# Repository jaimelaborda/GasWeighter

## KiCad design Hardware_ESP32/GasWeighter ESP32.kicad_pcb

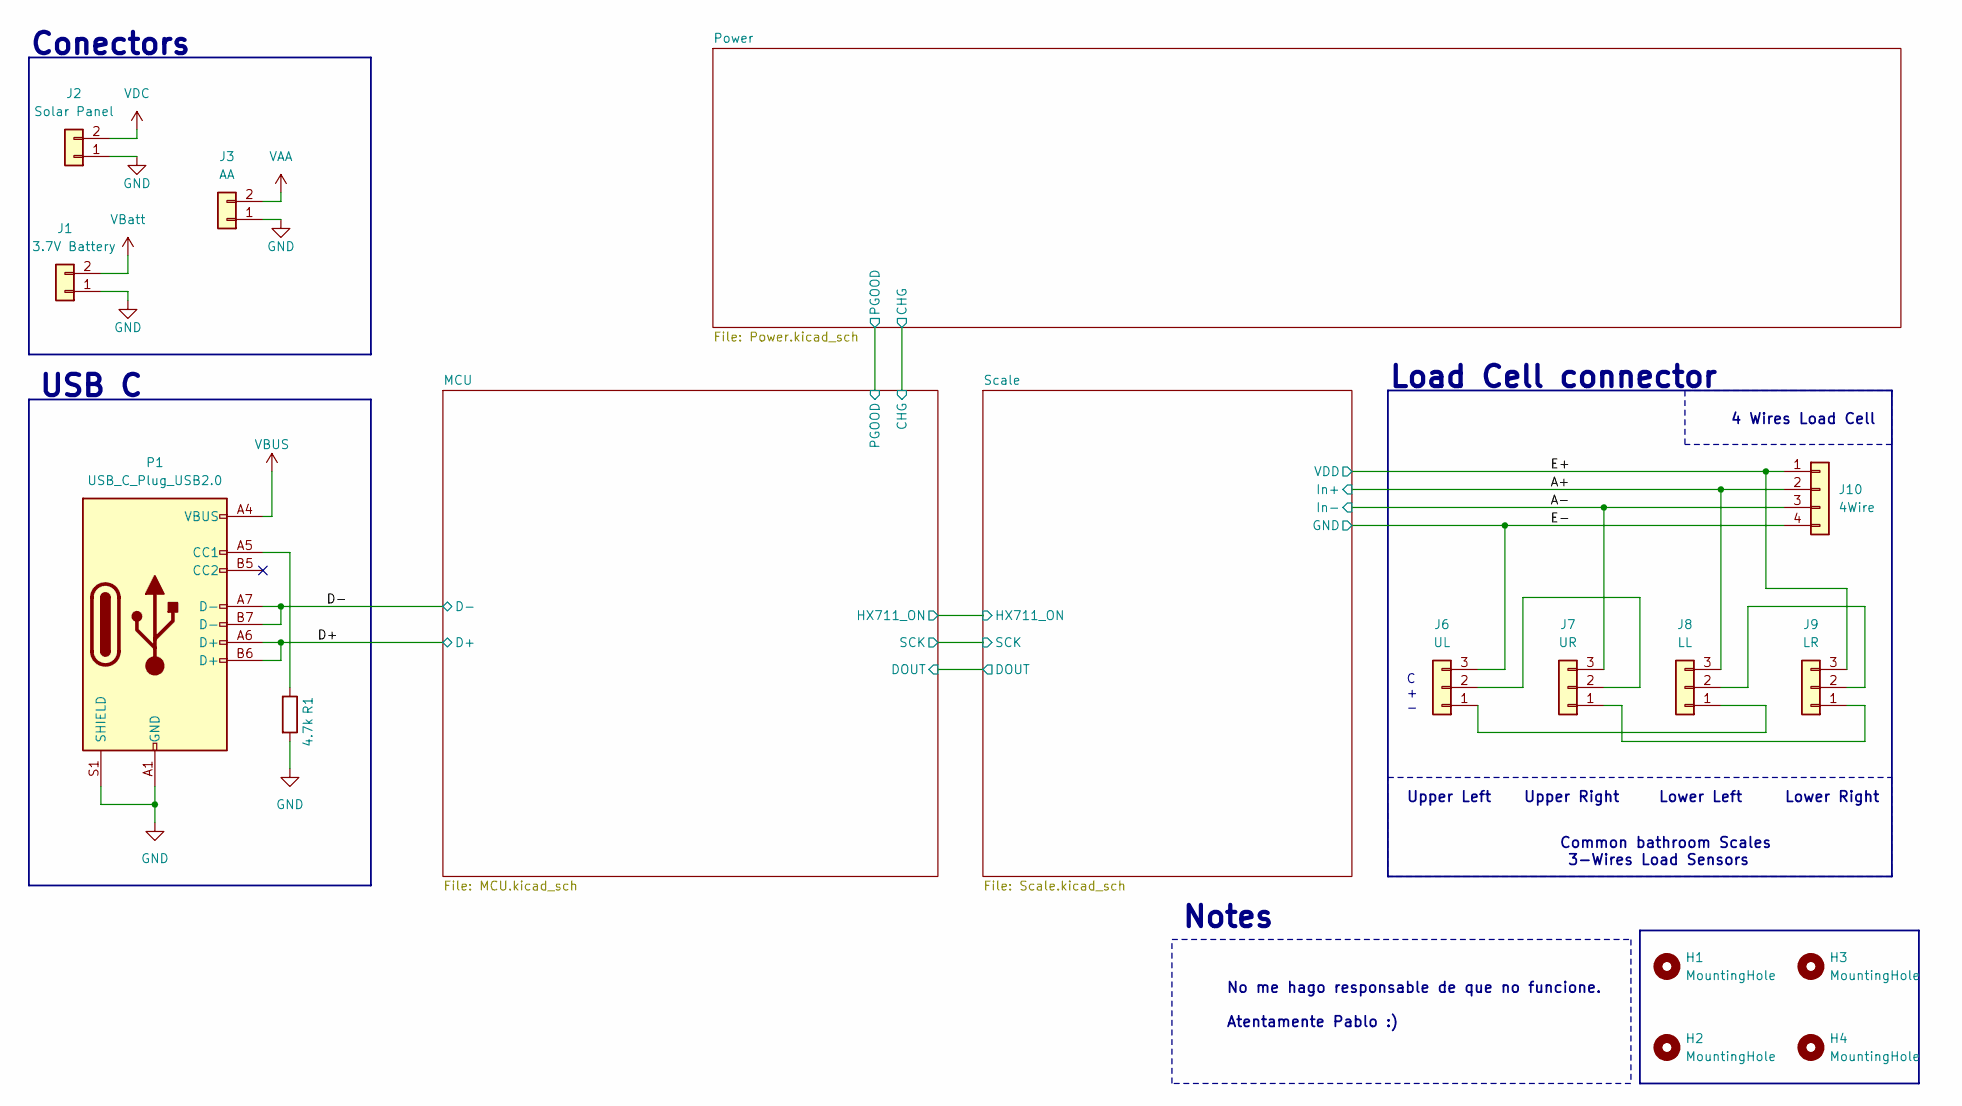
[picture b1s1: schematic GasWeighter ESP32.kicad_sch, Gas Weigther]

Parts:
H1, H2, H3, H4: MountingHole; MountingHole_3.2mm_M3_ISO7380
J1: 3.7V Battery; JST_PH_B2B-PH-K_1x02_P2.00mm_Vertical
J2: Solar Panel; JST_PH_B2B-PH-K_1x02_P2.00mm_Vertical
J3: AA; JST_PH_B2B-PH-K_1x02_P2.00mm_Vertical
J6: UL; JST_PH_B3B-PH-K_1x03_P2.00mm_Vertical
J7: UR; JST_PH_B3B-PH-K_1x03_P2.00mm_Vertical
J8: LL; JST_PH_B3B-PH-K_1x03_P2.00mm_Vertical
J9: LR; JST_PH_B3B-PH-K_1x03_P2.00mm_Vertical
J10: 4Wire; JST_PH_B4B-PH-K_1x04_P2.00mm_Vertical
P1: USB_C_Plug_USB2.0; USB C Molex_1
R1: 4.7k; R_0805_2012Metric_Pad1.20x1.40mm_HandSolder

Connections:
/A+: J8.3, J10.2; also elsewhere on the board
/A-: J7.3, J10.3; also elsewhere on the board
/D+: P1.A6 (D+), P1.B6 (D+); also elsewhere on the board
/D-: P1.A7 (D-), P1.B7 (D-); also elsewhere on the board
/E+: J9.3, J10.1; also elsewhere on the board
unnamed: J6.1, J8.1
unnamed: J6.2, J7.2
unnamed: J7.1, J9.1
unnamed: J8.2, J9.2
unnamed: P1.A5 (CC1), R1.1
VAA: J3.2; also elsewhere on the board
VBUS: P1.A4 (VBUS), P1.A9 (VBUS), P1.B4 (VBUS), P1.B9 (VBUS); also elsewhere on the board
VBatt: J1.2; also elsewhere on the board
VDC: J2.2; also elsewhere on the board

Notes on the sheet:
Common bathroom Scales 3-Wires Load Sensors
Notes
Upper Left
No me hago responsable de que no funcione. Atentamente Pablo :)
C + -
Load Cell connector
Conectors
USB C
Lower Left
Upper Right
4 Wires Load Cell
Lower Right

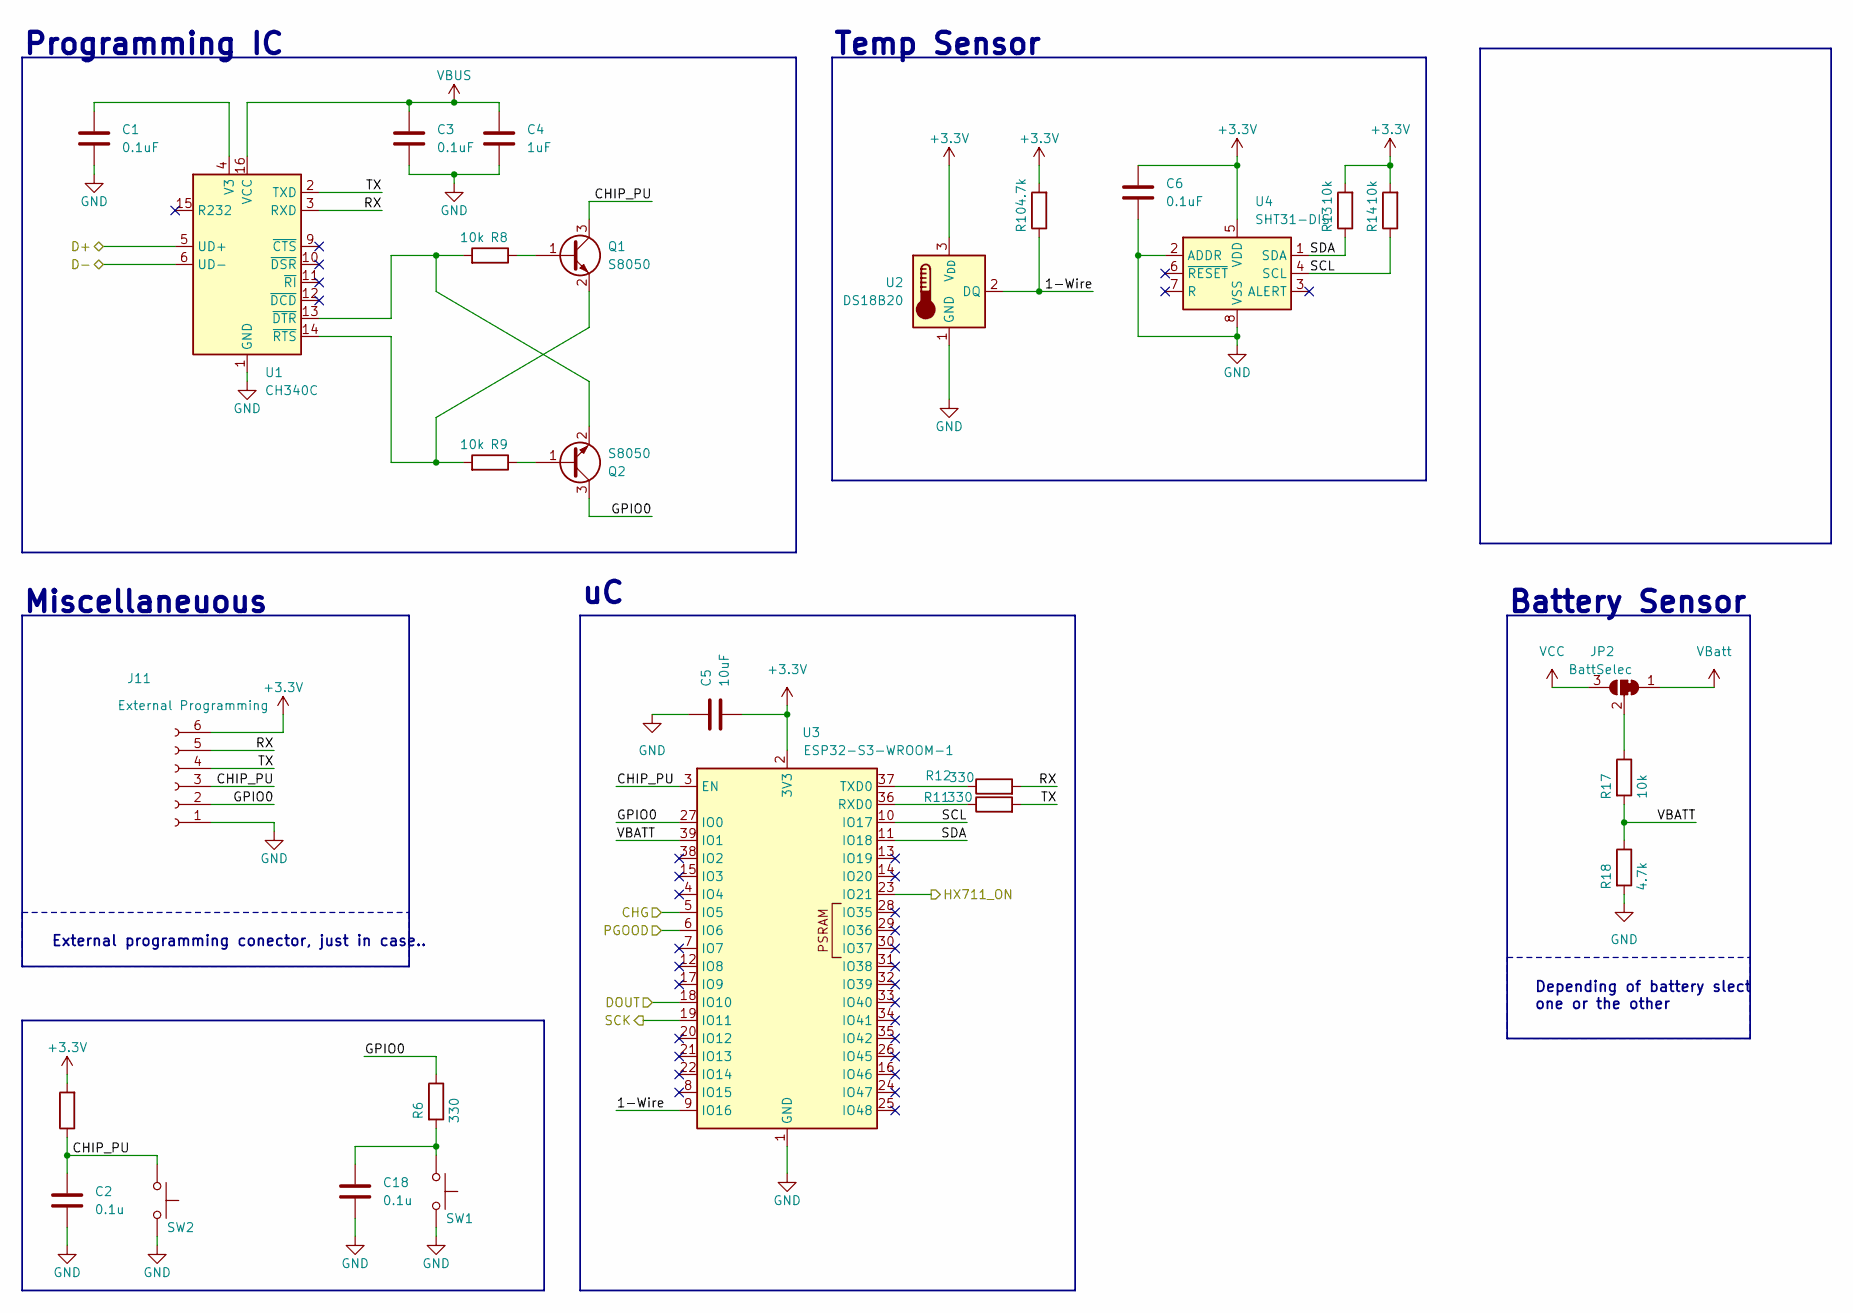
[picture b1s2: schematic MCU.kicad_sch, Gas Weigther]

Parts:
C1, C3, C6: 0.1uF; C_0805_2012Metric
C2, C18: 0.1u; C_0805_2012Metric
C4: 1uF; C_0805_2012Metric
C5: 10uF; C_0805_2012Metric
J11: External Programming; PinHeader_1x06_P2.54mm_Vertical
JP2: BattSelec; SolderJumper-3_P1.3mm_Bridged12_RoundedPad1.0x1.5mm
Q1, Q2: S8050; SOT-23
R5, R8, R9, R13, R14, R17: 10k; R_0805_2012Metric_Pad1.20x1.40mm_HandSolder
R6, R11, R12: 330; R_0805_2012Metric_Pad1.20x1.40mm_HandSolder
R10, R18: 4.7k; R_0805_2012Metric_Pad1.20x1.40mm_HandSolder
SW1, SW2: SW_Push; Button
U1: CH340C; SOIC-16_3.9x9.9mm_P1.27mm
U2: DS18B20; TO-92_Inline
U3: ESP32-S3-WROOM-1
U4: SHT31-DIS; Sensirion_DFN-8-1EP_2.5x2.5mm_P0.5mm_EP1.1x1.7mm

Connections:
/D+: U1.5 (UD+); also elsewhere on the board
/D-: U1.6 (UD-); also elsewhere on the board
/MCU/1-Wire: R10.1, U2.2 (DQ), U3.9 (IO16)
/MCU/CHG: U3.5 (IO5); also elsewhere on the board
/MCU/CHIP_PU: C2.1, J11.3, Q1.3 (C), R5.1, SW2.1, U3.3 (EN)
/MCU/DOUT: U3.18 (IO10); also elsewhere on the board
/MCU/GPIO0: J11.2, Q2.3 (C), R6.1, U3.27 (IO0)
/MCU/HX711_ON: U3.23 (IO21); also elsewhere on the board
/MCU/PGOOD: U3.6 (IO6); also elsewhere on the board
/MCU/RX: J11.5, R12.2, U1.3 (RXD)
/MCU/SCK: U3.19 (IO11); also elsewhere on the board
/MCU/SCL: R14.1, U3.10 (IO17), U4.4 (SCL)
/MCU/SDA: R13.1, U3.11 (IO18), U4.1 (SDA)
/MCU/TX: J11.4, R11.2, U1.2 (TXD)
/MCU/VBATT: R17.2, R18.1, U3.39 (IO1)
unnamed: C18.1, R6.2, SW1.1
unnamed: JP2.2 (C), R17.1
unnamed: Q1.1 (B), R8.1
unnamed: Q1.2 (E), R9.2, U1.14 (~RTS)
unnamed: Q2.1 (B), R9.1
unnamed: Q2.2 (E), R8.2, U1.13 (~DTR)
unnamed: C1.1, U1.4 (V3)
unnamed: R11.1, U3.36 (RXD0)
unnamed: R12.1, U3.37 (TXD0)
VBUS: C3.1, C4.1, U1.16 (VCC); also elsewhere on the board
VBatt: JP2.1 (A); also elsewhere on the board
VCC: JP2.3 (B); also elsewhere on the board

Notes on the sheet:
Programming IC
Temp Sensor
External programming conector, just in case..
Miscellaneuous
Battery Sensor
Depending of battery slect one or the other

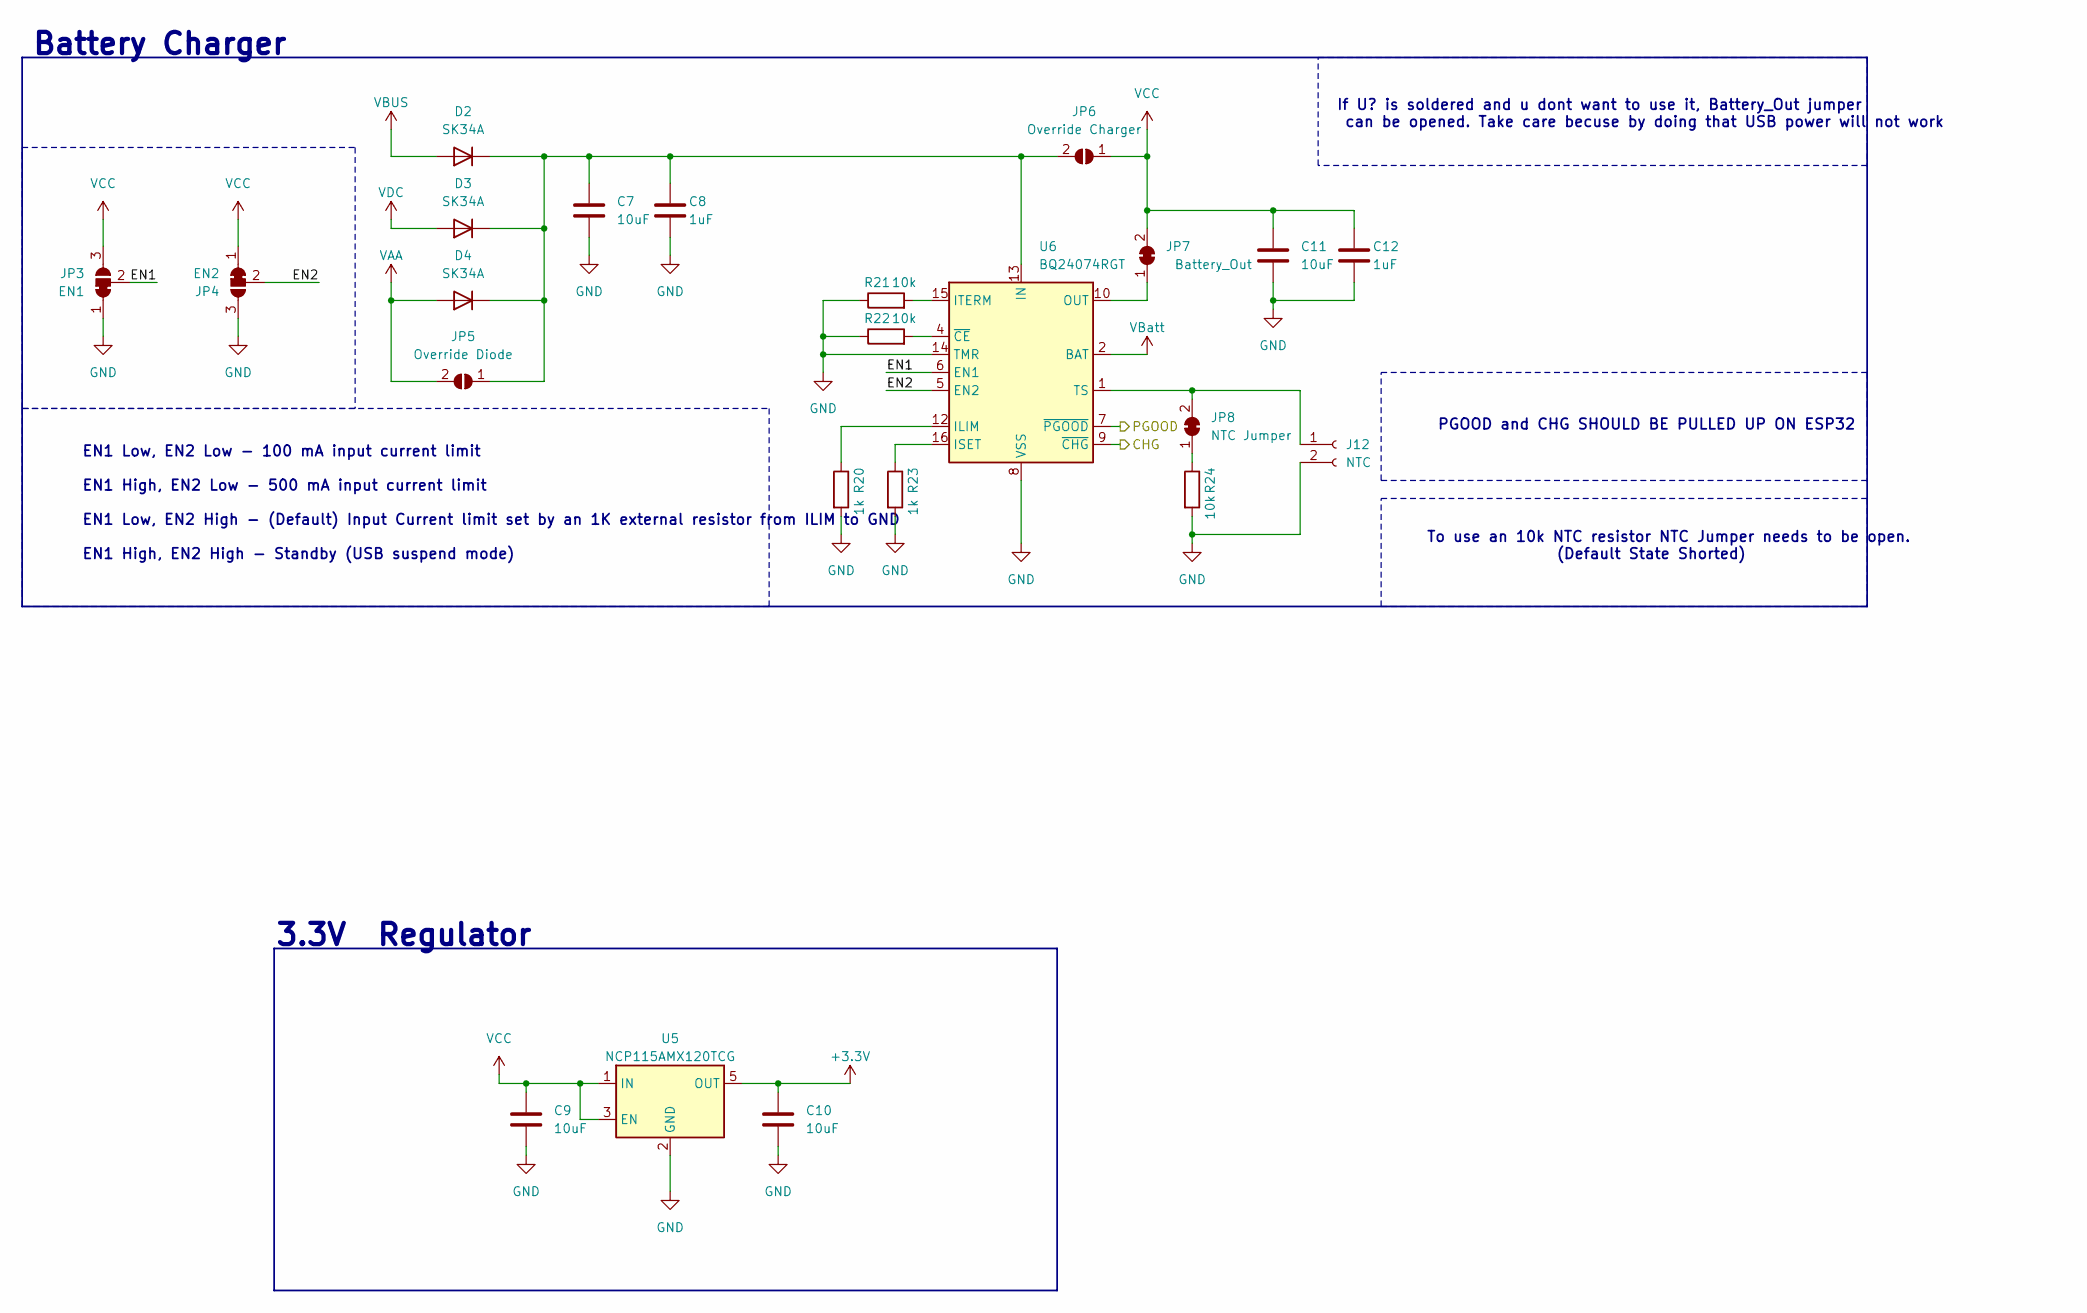
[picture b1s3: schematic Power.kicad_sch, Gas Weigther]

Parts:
C7, C11: 10uF; C_0603_1608Metric_Pad1.08x0.95mm_HandSolder
C8, C12: 1uF; C_0603_1608Metric_Pad1.08x0.95mm_HandSolder
C9, C10: 10uF; C_0805_2012Metric
D2, D3, D4: SK34A; D_0805_2012Metric
J12: NTC; JST_PH_B2B-PH-K_1x02_P2.00mm_Vertical
JP3: EN1; SolderJumper-3_P1.3mm_Bridged12_RoundedPad1.0x1.5mm
JP4: EN2; SolderJumper-3_P1.3mm_Bridged12_RoundedPad1.0x1.5mm
JP5: Override Diode; SolderJumper-2_P1.3mm_Open_RoundedPad1.0x1.5mm
JP6: Override Charger; SolderJumper-2_P1.3mm_Open_RoundedPad1.0x1.5mm
JP7: Battery_Out; SolderJumper-2_P1.3mm_Bridged_RoundedPad1.0x1.5mm
JP8: NTC Jumper; SolderJumper-2_P1.3mm_Bridged_RoundedPad1.0x1.5mm
R20, R23: 1k; R_0805_2012Metric_Pad1.20x1.40mm_HandSolder
R21, R22, R24: 10k; R_0805_2012Metric_Pad1.20x1.40mm_HandSolder
U5: NCP115AMX120TCG; SOT-23-5_HandSoldering
U6: BQ24074RGT; VQFN-16-1EP_3x3mm_P0.5mm_EP1.6x1.6mm

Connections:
/MCU/CHG: U6.9 (~CHG); also elsewhere on the board
/MCU/PGOOD: U6.7 (~PGOOD); also elsewhere on the board
/Power/EN1: JP3.2 (C), U6.6 (EN1)
/Power/EN2: JP4.2 (C), U6.5 (EN2)
unnamed: C7.1, C8.1, D2.1 (K), D3.1 (K), D4.1 (K), JP5.1 (A), JP6.2 (B), U6.13 (IN)
unnamed: J12.1, JP8.2 (B), U6.1 (TS)
unnamed: JP7.1 (A), U6.10 (OUT), U6.11 (OUT)
unnamed: JP8.1 (A), R24.1
unnamed: R20.1, U6.12 (ILIM)
unnamed: R23.1, U6.16 (ISET)
unnamed: R21.2, U6.15 (ITERM)
unnamed: R22.2, U6.4 (~CE)
VAA: D4.2 (A), JP5.2 (B); also elsewhere on the board
VBUS: D2.2 (A); also elsewhere on the board
VBatt: U6.2 (BAT), U6.3 (BAT); also elsewhere on the board
VCC: C9.1, C11.1, C12.1, JP3.3 (B), JP4.1 (A), JP6.1 (A), JP7.2 (B), U5.1 (IN), U5.3 (EN); also elsewhere on the board
VDC: D3.2 (A); also elsewhere on the board

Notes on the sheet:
Battery Charger
EN1 Low, EN2 Low - 100 mA input current limit EN1 High, EN2 Low - 500 mA input current limit EN1 Low, EN2 High - (Default) Input Current limit set by an 1K external resistor from ILIM to GND EN1 High, EN2 High - Standby (USB suspend mode)
3.3V Regulator
If U? is soldered and u dont want to use it, Battery_Out jumper can be opened. Take care becuse by doing that USB power will not work
PGOOD and CHG SHOULD BE PULLED UP ON ESP32
To use an 10k NTC resistor NTC Jumper needs to be open. (Default State Shorted)

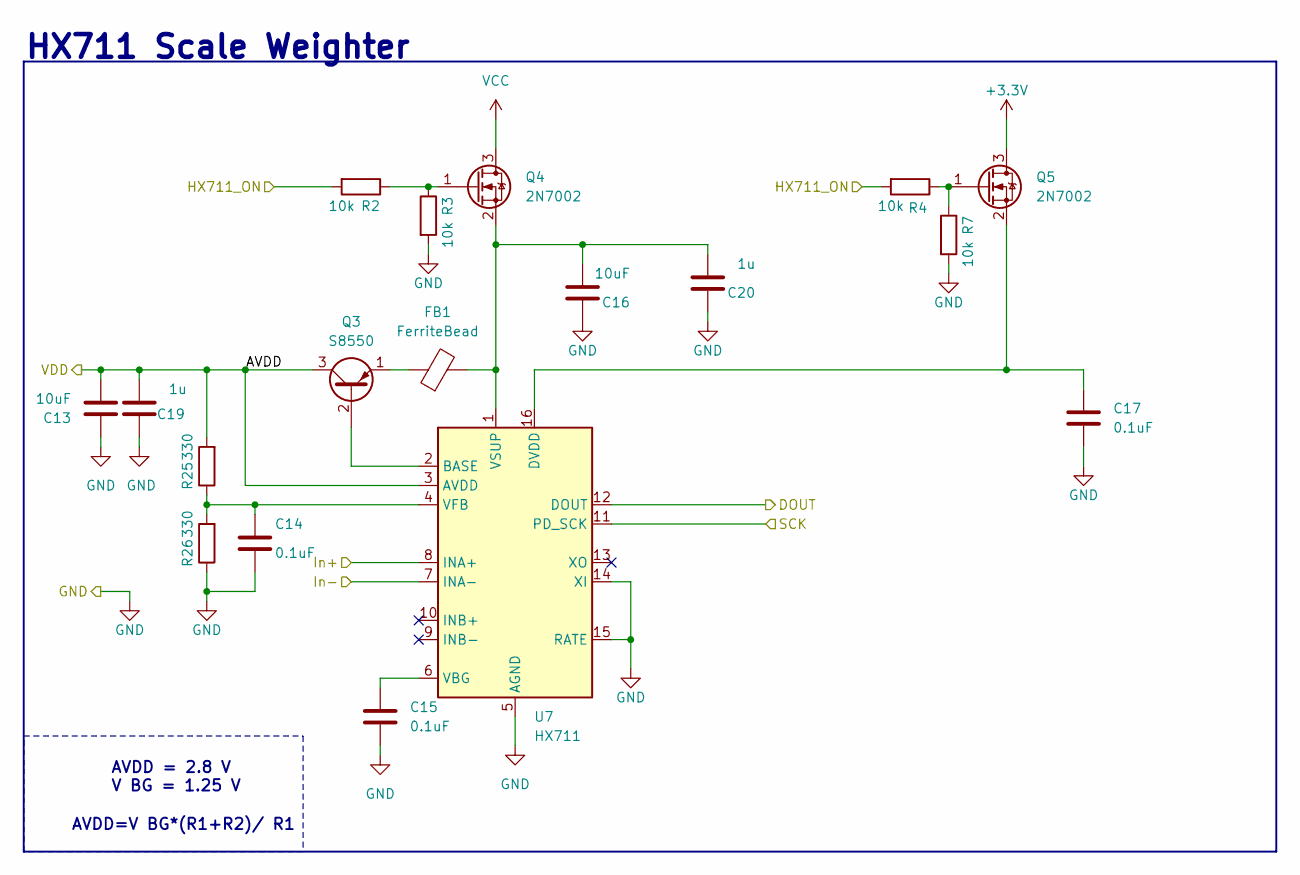
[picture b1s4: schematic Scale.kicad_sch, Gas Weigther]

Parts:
C13, C16: 10uF; C_0805_2012Metric
C14, C15, C17: 0.1uF; C_0805_2012Metric
C19, C20: 1u; C_0805_2012Metric
FB1: FerriteBead; L_0805_2012Metric
Q3: S8550; SOT-23
Q4, Q5: 2N7002; SOT-23
R2, R3, R4, R7: 10k; R_0805_2012Metric_Pad1.20x1.40mm_HandSolder
R25, R26: 330; R_0805_2012Metric_Pad1.20x1.40mm_HandSolder
U7: HX711; SOP-16_3.9x9.9mm_P1.27mm

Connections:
/A+: U7.8 (INA+); also elsewhere on the board
/A-: U7.7 (INA-); also elsewhere on the board
/E+: C13.2, C19.2, Q3.3 (C), R25.2, U7.3 (AVDD); also elsewhere on the board
/MCU/DOUT: U7.12 (DOUT); also elsewhere on the board
/MCU/HX711_ON: R2.2, R4.2; also elsewhere on the board
/MCU/SCK: U7.11 (PD_SCK); also elsewhere on the board
unnamed: Q3.2 (B), U7.2 (BASE)
unnamed: FB1.1, Q3.1 (E)
unnamed: Q4.1 (G), R2.1, R3.1
unnamed: C16.2, C20.2, FB1.2, Q4.2 (S), U7.1 (VSUP)
unnamed: Q5.1 (G), R4.1, R7.1
unnamed: C17.1, Q5.2 (S), U7.16 (DVDD)
unnamed: C15.1, U7.6 (VBG)
unnamed: C14.1, R25.1, R26.2, U7.4 (VFB)
VCC: Q4.3 (D); also elsewhere on the board

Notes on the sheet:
AVDD=V BG*(R1+R2)/ R1
HX711 Scale Weighter
AVDD = 2.8 V V BG = 1.25 V

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
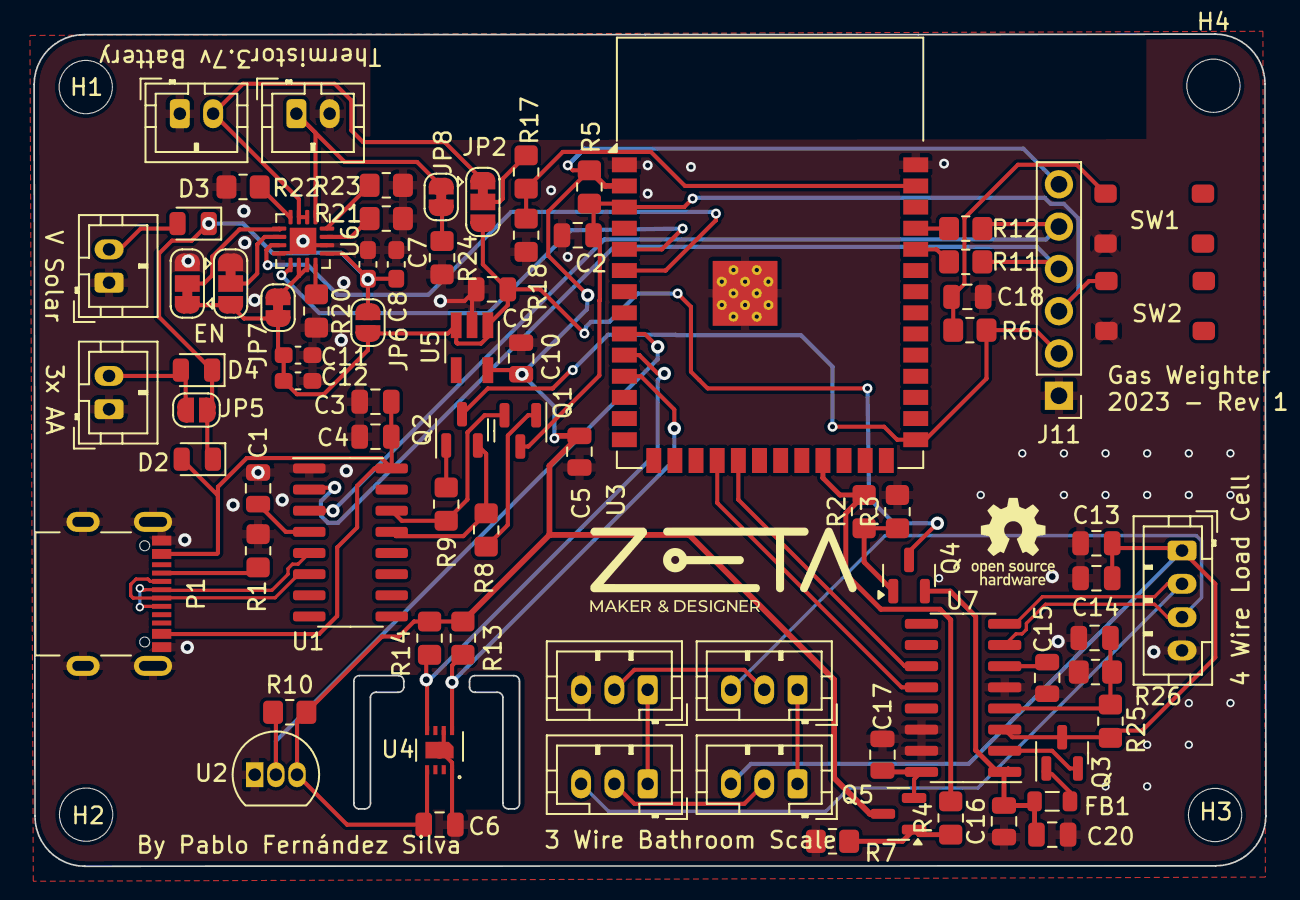
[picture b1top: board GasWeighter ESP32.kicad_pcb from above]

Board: 2 copper layers, 74.0 x 50.0 mm, 83 parts (0 on the bottom side), 57 nets.

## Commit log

2023-11-11 Organized
2023-11-12 3Cents USB
2023-11-12 Gerbers
2024-08-29 ESP32 HW added
    Added a hardware version with ESP32-S3 microcontroller
2024-09-15 First Firmware
2024-09-15 Creation of dev branch
2024-09-15 Code refactored so that scale HAL is better abstracted from the rest of the program (Not tested)
